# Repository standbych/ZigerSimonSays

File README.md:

# ZigerSimonSays
Simon Says Clone

Requirements
- https://github.com/adafruit/Adafruit-GFX-Library
- https://github.com/adafruit/Adafruit_SSD1306

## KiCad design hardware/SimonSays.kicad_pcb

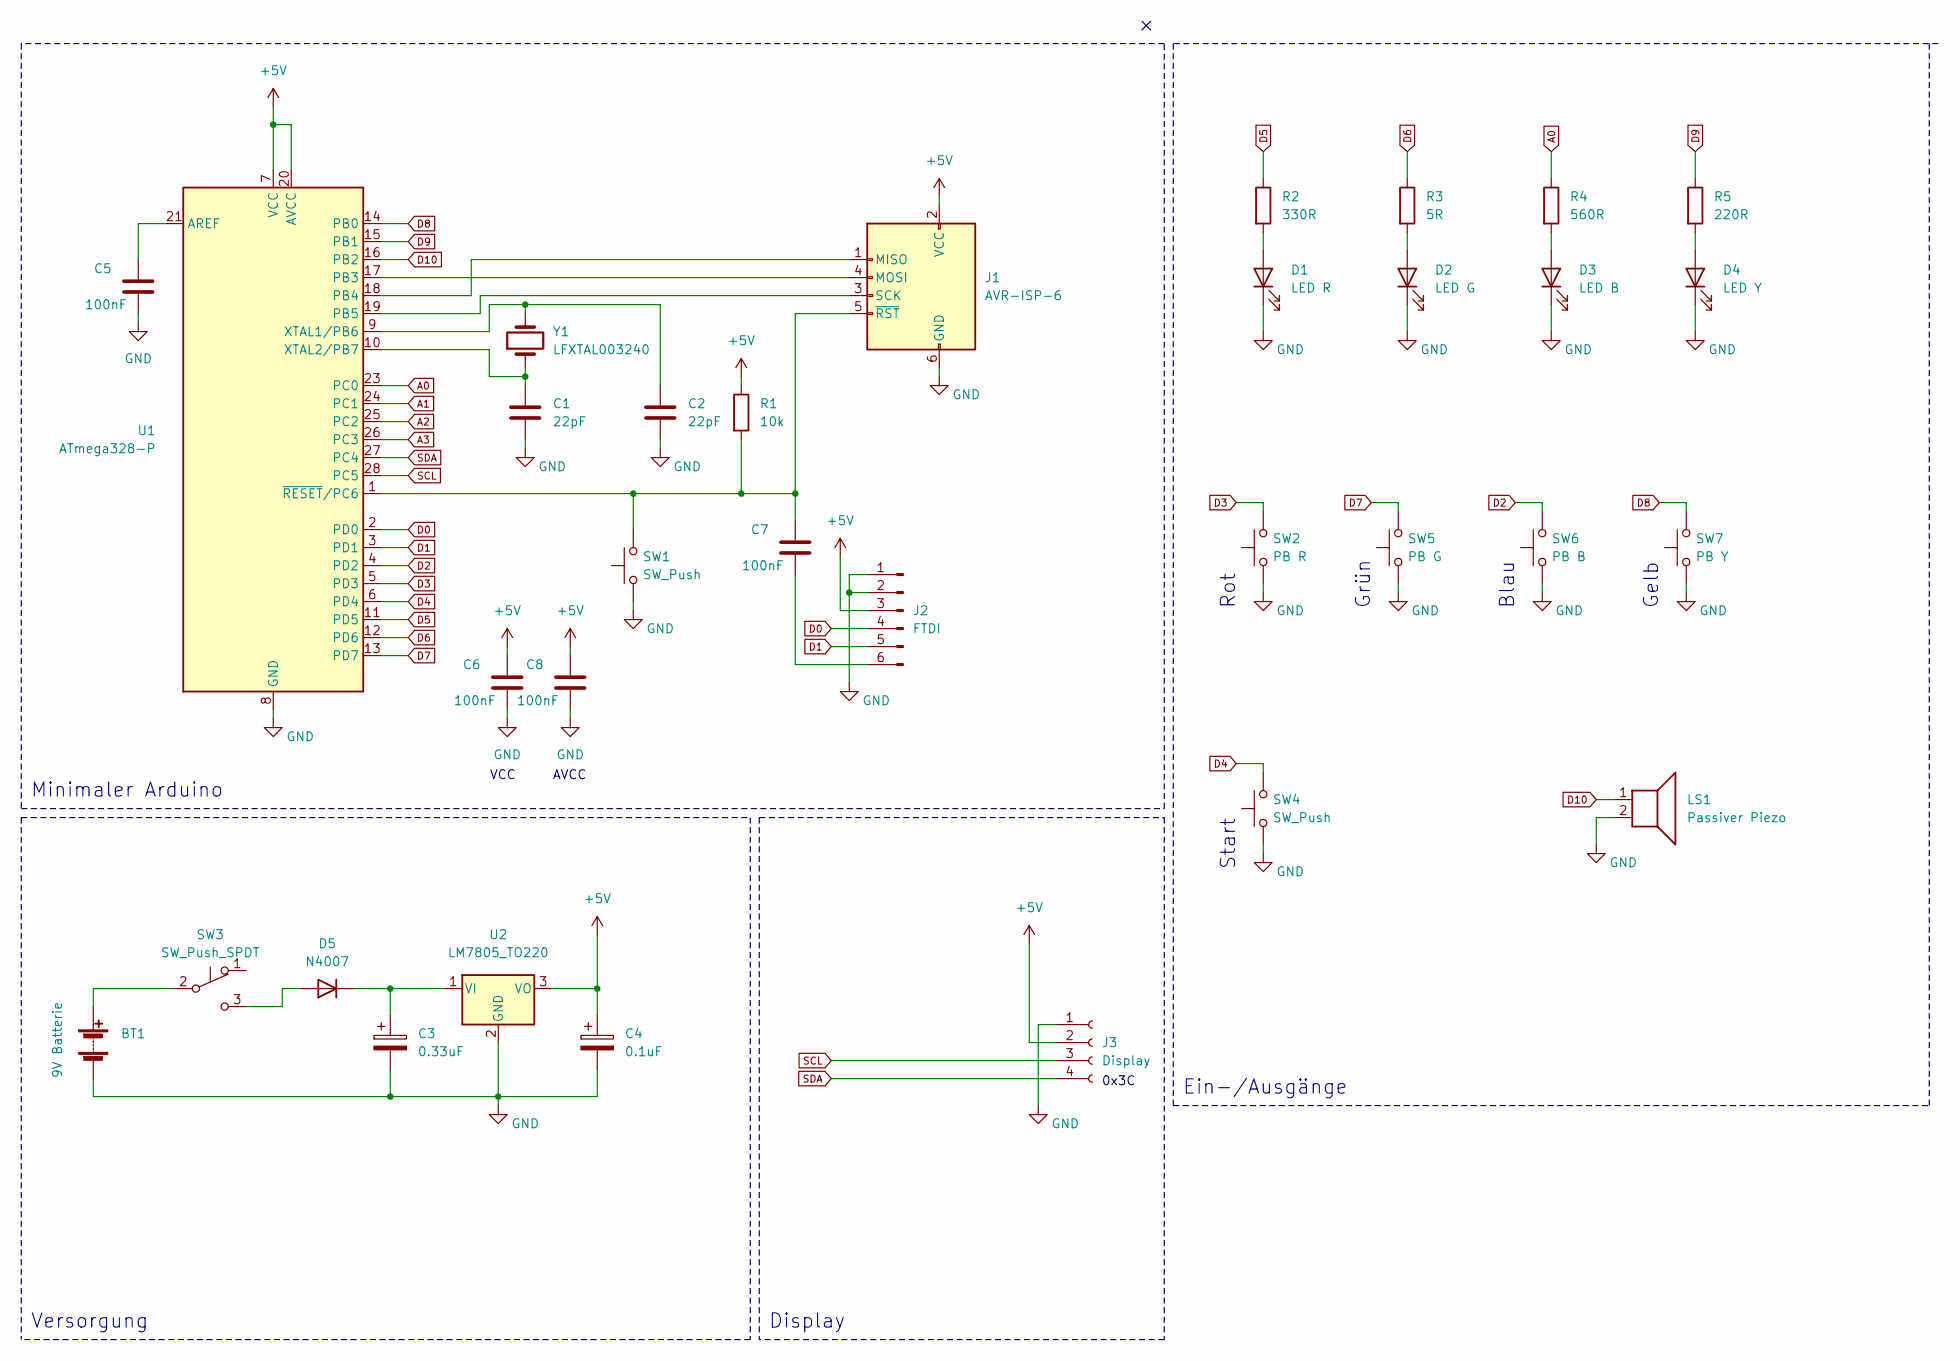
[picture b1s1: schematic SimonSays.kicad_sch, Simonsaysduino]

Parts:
BT1: 9V Batterie; BatteryHolder_Eagle_12BH611-GR; Manufacturer Part Number MP000351
C1, C2: 22pF; C_Disc_D5.0mm_W2.5mm_P2.50mm
C3: 0.33uF; CP_Radial_D5.0mm_P2.50mm
C4: 0.1uF; CP_Radial_D5.0mm_P2.50mm
C5, C6, C7, C8: 100nF; C_Disc_D5.0mm_W2.5mm_P2.50mm
D1: LED R; LED_D10.0mm
D2: LED G; LED_D10.0mm
D3: LED B; LED_D10.0mm
D4: LED Y; LED_D10.0mm
D5: N4007; D_5W_P10.16mm_Horizontal
J1: AVR-ISP-6; PinHeader_2x03_P2.54mm_Vertical
J2: FTDI; PinHeader_1x06_P2.54mm_Vertical
J3: Display; Display_128x64_096_I2C_no_holes
LS1: Passiver Piezo; Buzzer_12x9.5RM7.6
R1: 10k; R_Axial_DIN0207_L6.3mm_D2.5mm_P10.16mm_Horizontal
R2: 330R; R_Axial_DIN0207_L6.3mm_D2.5mm_P10.16mm_Horizontal
R3: 5R; R_Axial_DIN0207_L6.3mm_D2.5mm_P10.16mm_Horizontal
R4: 560R; R_Axial_DIN0207_L6.3mm_D2.5mm_P10.16mm_Horizontal
R5: 220R; R_Axial_DIN0207_L6.3mm_D2.5mm_P10.16mm_Horizontal
SW1: SW_Push; SW_PUSH_6mm
SW2: PB R; Button_12*12*7.3_red_round
SW3: SW_Push_SPDT; cheap_china_slide_switch
SW4: SW_Push; Button_12*12*7.3_white_round
SW5: PB G; Button_12*12*7.3_green_round
SW6: PB B; Button_12*12*7.3_blue_round
SW7: PB Y; Button_12*12*7.3_yellow_round
U1: ATmega328-P; DIP-28_W7.62mm
U2: LM7805_TO220; TO-220-3_Horizontal_TabDown
Y1: LFXTAL003240; Crystal_HC50_Vertical

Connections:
+5V: C4.1, C6.1, C8.1, J1.2 (VCC), J2.3, J3.2, R1.1, U1.7 (VCC), U1.20 (AVCC), U2.3 (VO)
A0: R4.1, U1.23 (PC0)
A1: U1.24 (PC1)
A2: U1.25 (PC2)
A3: U1.26 (PC3)
D0: J2.4, U1.2 (PD0)
D1: J2.5, U1.3 (PD1)
D2: SW6.2, U1.4 (PD2)
D3: SW2.2, U1.5 (PD3)
D4: SW4.2, U1.6 (PD4)
D5: R2.1, U1.11 (PD5)
D6: R3.1, U1.12 (PD6)
D7: SW5.2, U1.13 (PD7)
D8: SW7.2, U1.14 (PB0)
D9: R5.1, U1.15 (PB1)
D10: LS1.1, U1.16 (PB2)
GND: BT1.2 (-), C1.2, C2.2, C3.2, C4.2, C5.2, C6.2, C8.2, D1.1 (K), D2.1 (K), D3.1 (K), D4.1 (K), J1.6 (GND), J2.1, J2.2, J3.1, LS1.2, SW1.1, SW2.1, SW4.1, SW5.1, SW6.1, SW7.1, U1.8 (GND), U1.22 (GND), U2.2 (GND)
unnamed: BT1.1 (+), SW3.2 (B)
unnamed: C1.1, U1.10 (XTAL2/PB7), Y1.1
unnamed: C2.1, U1.9 (XTAL1/PB6), Y1.2
unnamed: C3.1, D5.1 (K), U2.1 (VI)
unnamed: C5.1, U1.21 (AREF)
unnamed: C7.1, J1.5 (~RST), R1.2, SW1.2, U1.1 (~RESET/PC6)
unnamed: C7.2, J2.6
unnamed: D1.2 (A), R2.2
unnamed: D2.2 (A), R3.2
unnamed: D3.2 (A), R4.2
unnamed: D4.2 (A), R5.2
unnamed: D5.2 (A), SW3.3 (C)
unnamed: J1.1 (MISO), U1.18 (PB4)
unnamed: J1.3 (SCK), U1.19 (PB5)
unnamed: J1.4 (MOSI), U1.17 (PB3)
SCL: J3.3, U1.28 (PC5)
SDA: J3.4, U1.27 (PC4)

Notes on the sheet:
Minimaler Arduino
Versorgung
VCC
AVCC
Display
0x3C
Ein-/Ausgänge
Rot
Start
Grün
Blau
Gelb

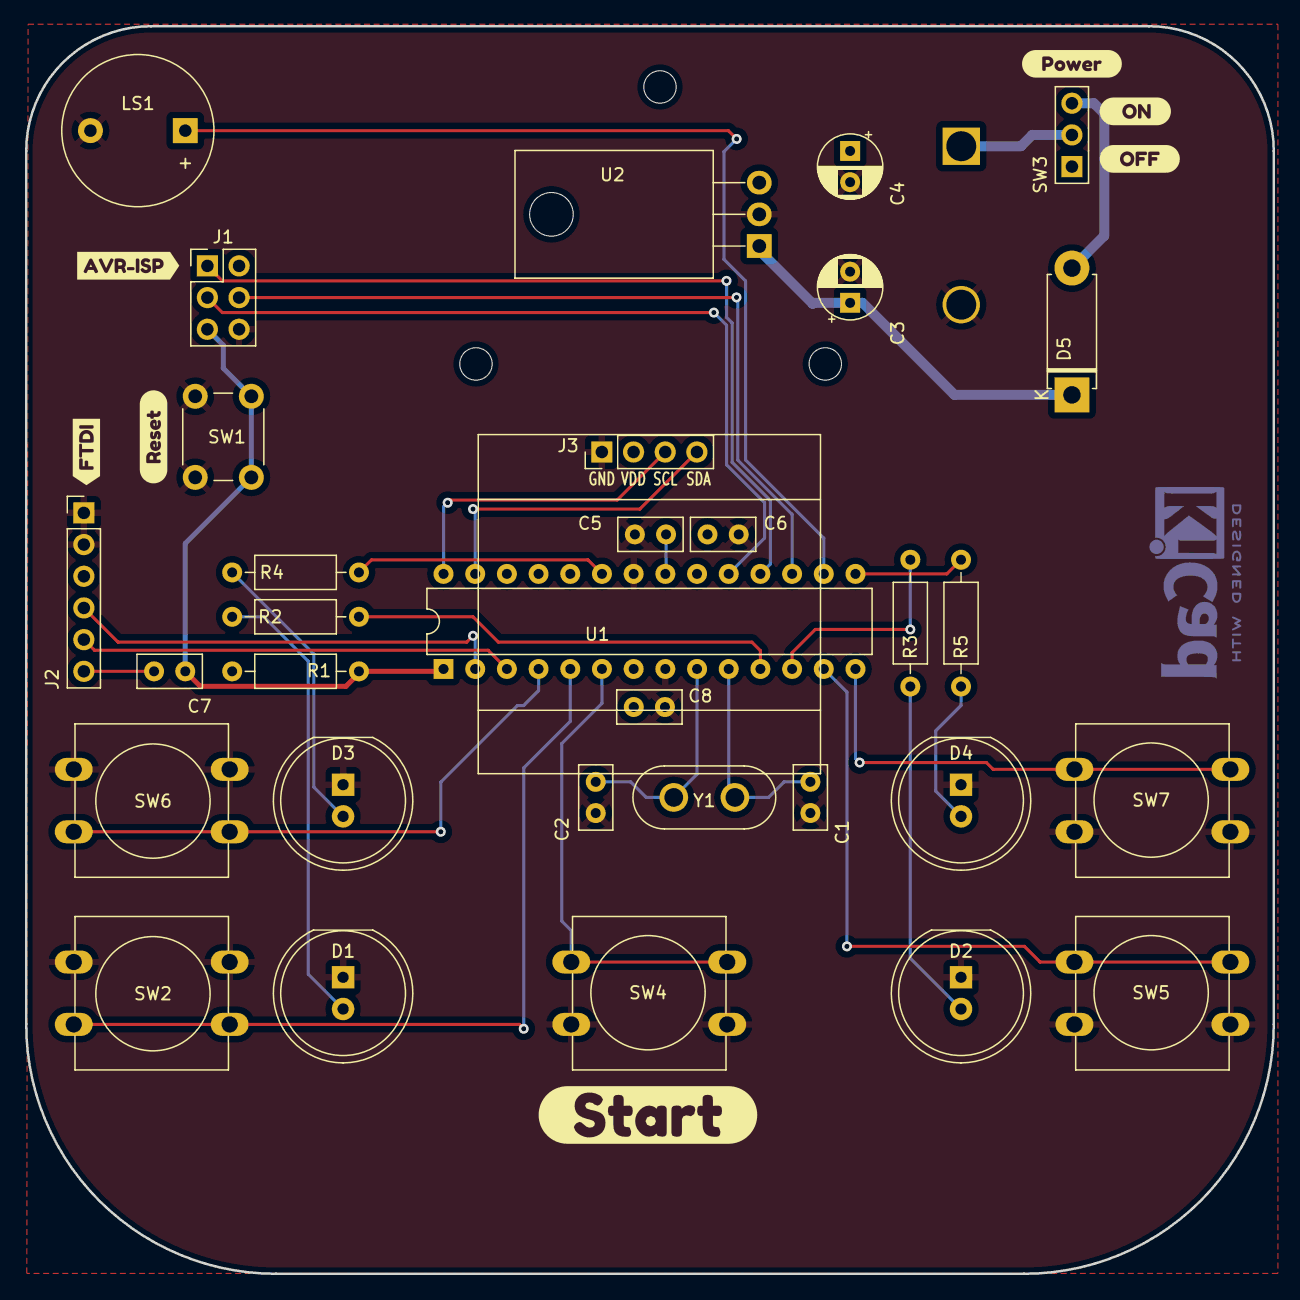
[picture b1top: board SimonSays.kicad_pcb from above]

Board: 2 copper layers, 100.0 x 100.0 mm, 40 parts (1 on the bottom side), 31 nets.

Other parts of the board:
kibuzzard-6160B6E4: G***; kibuzzard-6160B6E4
kibuzzard-6160B38A: G***; kibuzzard-6160B38A
kibuzzard-6160B392: G***; kibuzzard-6160B392
kibuzzard-61609DB8: G***; kibuzzard-61609DB8
kibuzzard-61609DF8: G***; kibuzzard-61609DF8
kibuzzard-61609E2B: G***; kibuzzard-61609E2B
kibuzzard-61609E4D: G***; kibuzzard-61609E4D

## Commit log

2022-02-08 Hardware files
2022-02-09 Migrate from Local Repo
2024-11-10 Gameplay angepasst
2024-11-11 Gameplay optimiert
2024-12-02 SimonSays überarbeitet
2024-12-02 Cleanup
2024-12-02 PDI Version
2024-12-02 kleine Anpassungen
